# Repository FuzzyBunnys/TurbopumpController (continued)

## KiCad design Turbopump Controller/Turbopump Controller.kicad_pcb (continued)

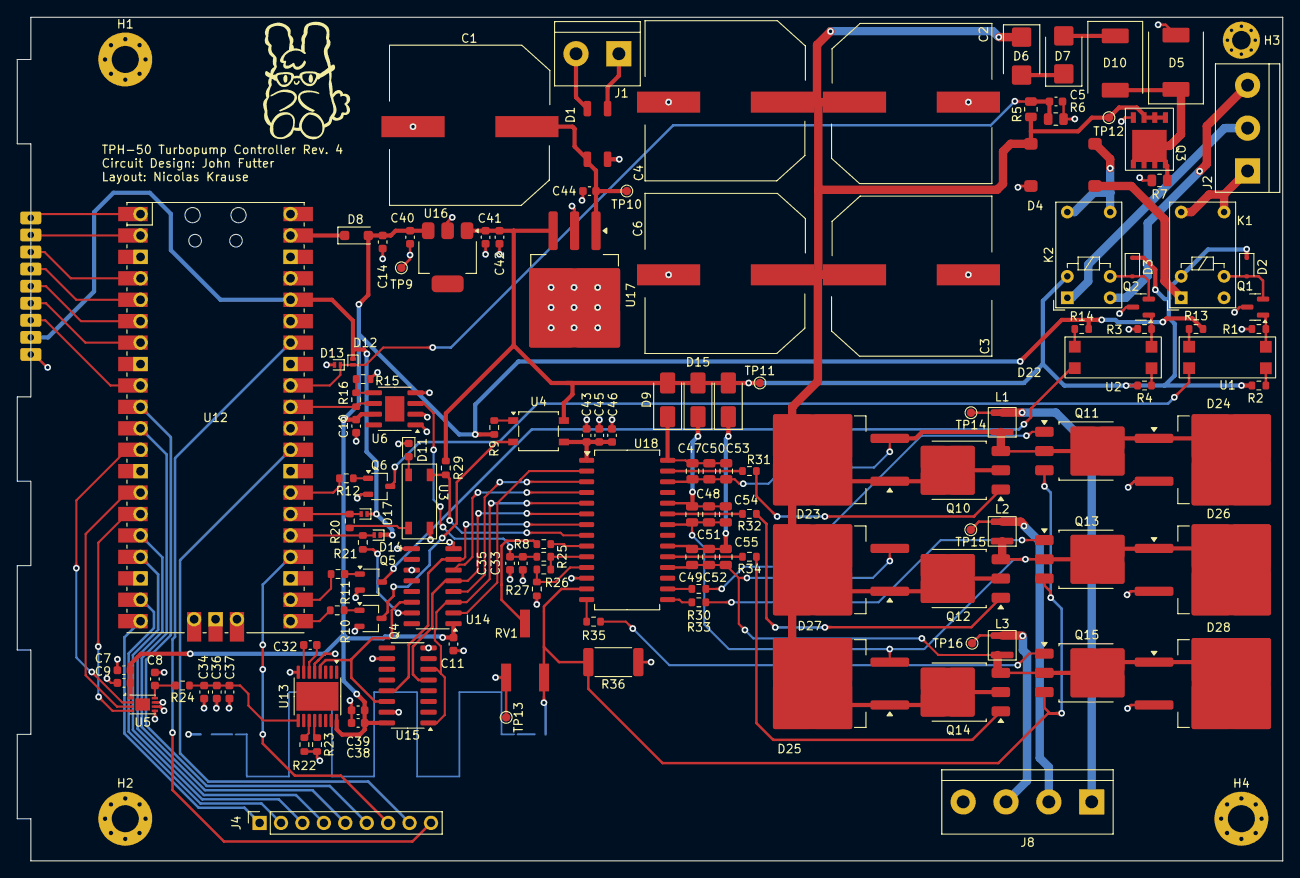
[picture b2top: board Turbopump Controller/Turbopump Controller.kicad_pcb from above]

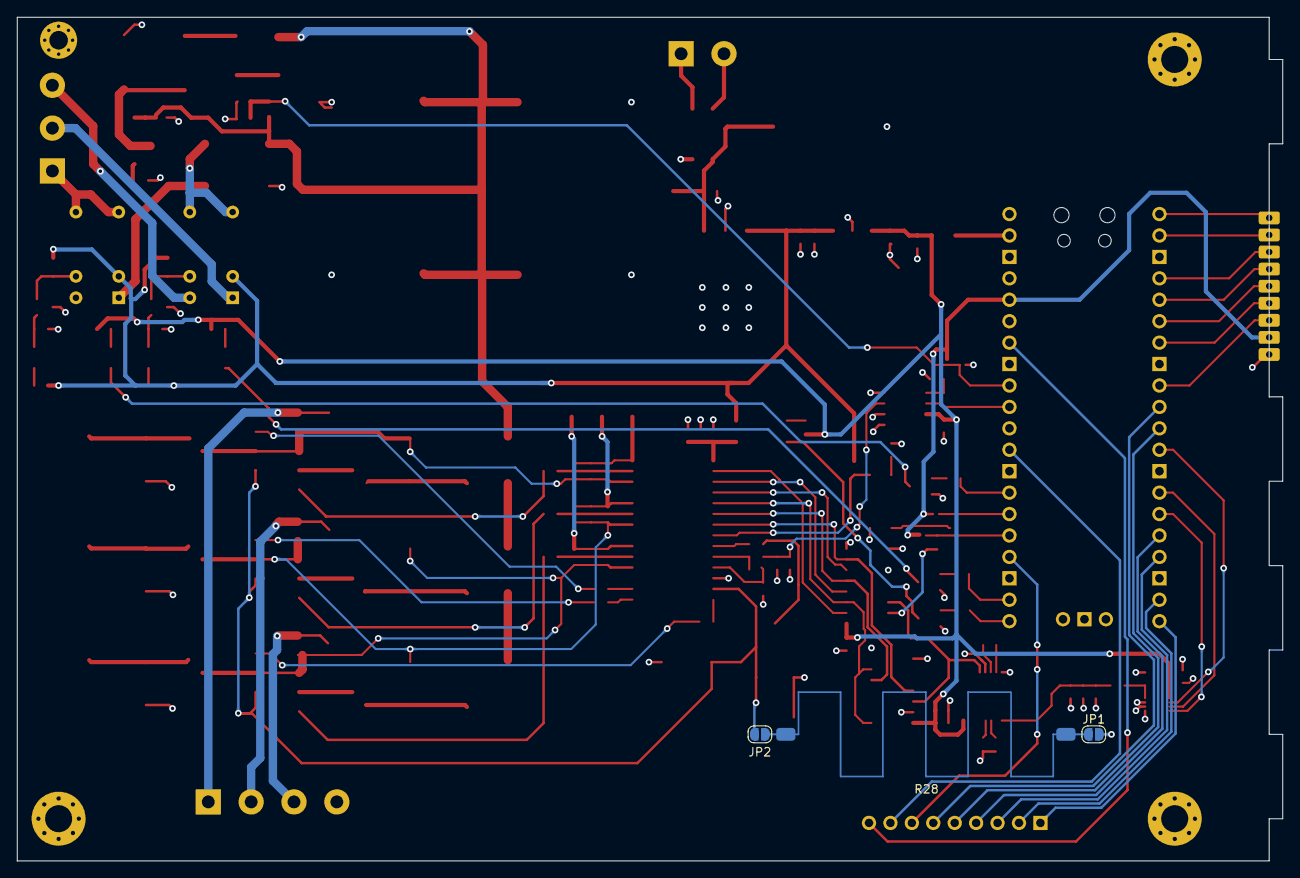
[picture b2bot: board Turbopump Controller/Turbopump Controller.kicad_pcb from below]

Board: 4 copper layers, 150.0 x 100.0 mm, 142 parts (3 on the bottom side), 106 nets.

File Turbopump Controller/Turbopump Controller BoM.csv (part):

"Source:","C:\Users\fuzzy\Documents\Fusor\Fusor Sensors\Turbopump Controller Complete\Turbopump Controller\Turbopump Controller.kicad_sch"
"Date:","2024-02-09 11:35:52 AM"
"Tool:","Eeschema (6.0.0)"
"Generator:","C:\Program Files\KiCad\6.0\bin\scripting\plugins/bom_csv_grouped_by_value.py"
"Component Count:","120"

"Individual Components:"

"Item","Qty","Reference(s)","Value","LibPart","Footprint","Datasheet"
"","","C1","330uF 100v","Device:C_Polarized_US","","~"
"","","C2","330uF 100v","Device:C_Polarized_US","","~"
"","","C3","330uF 100v","Device:C_Polarized_US","","~"
"","","C4","330uF 100v","Device:C_Polarized_US","","~"
"","","C5","0.1u","Device:C","Capacitor_SMD:C_0603_1608Metric_Pad1.08x0.95mm_HandSolder","~"
"","","C6","330uF 100v","Device:C_Polarized_US","","~"
"","","C7","0.1u","Device:C","","~"
"","","C8","1u","Device:C","","~"
"","","C9","10u","Device:C","","~"
"","","C14","4.7u","Device:C","Capacitor_SMD:C_0603_1608Metric_Pad1.08x0.95mm_HandSolder","~"
"","","C32","3.9n","Device:C","Capacitor_SMD:C_0603_1608Metric_Pad1.08x0.95mm_HandSolder","~"
"","","C33","4.7u","Device:C","Capacitor_SMD:C_0603_1608Metric_Pad1.08x0.95mm_HandSolder","~"
"","","C34","4.7u","Device:C","Capacitor_SMD:C_0603_1608Metric_Pad1.08x0.95mm_HandSolder","~"
"","","C35","4.7u","Device:C","Capacitor_SMD:C_0603_1608Metric_Pad1.08x0.95mm_HandSolder","~"
"","","C36","4.7u","Device:C","Capacitor_SMD:C_0603_1608Metric_Pad1.08x0.95mm_HandSolder","~"
"","","C37","4.7u","Device:C","Capacitor_SMD:C_0603_1608Metric_Pad1.08x0.95mm_HandSolder","~"
"","","C38","4.7u","Device:C","Capacitor_SMD:C_0603_1608Metric_Pad1.08x0.95mm_HandSolder","~"
"","","C39","4.7u","Device:C","Capacitor_SMD:C_0603_1608Metric_Pad1.08x0.95mm_HandSolder","~"
"","","C40","4.7u","Device:C","Capacitor_SMD:C_0603_1608Metric_Pad1.08x0.95mm_HandSolder","~"
"","","C41","4.7u","Device:C","Capacitor_SMD:C_0603_1608Metric_Pad1.08x0.95mm_HandSolder","~"
"","","C42","4.7u","Device:C","Capacitor_SMD:C_0603_1608Metric_Pad1.08x0.95mm_HandSolder","~"
"","","C43","4.7u","Device:C","Capacitor_SMD:C_0603_1608Metric_Pad1.08x0.95mm_HandSolder","~"
"","","C44","4.7u","Device:C","Capacitor_SMD:C_0603_1608Metric_Pad1.08x0.95mm_HandSolder","~"
"","","C45","4.7u","Device:C","Capacitor_SMD:C_0603_1608Metric_Pad1.08x0.95mm_HandSolder","~"
"","","C46","4.7u","Device:C","Capacitor_SMD:C_0603_1608Metric_Pad1.08x0.95mm_HandSolder","~"
"","","C47","4.7u","Device:C","Capacitor_SMD:C_0603_1608Metric_Pad1.08x0.95mm_HandSolder","~"
"","","C48","4.7u","Device:C","Capacitor_SMD:C_0603_1608Metric_Pad1.08x0.95mm_HandSolder","~"
"","","C49","4.7u","Device:C","Capacitor_SMD:C_0603_1608Metric_Pad1.08x0.95mm_HandSolder","~"
"","","C50","4.7u","Device:C","Capacitor_SMD:C_0603_1608Metric_Pad1.08x0.95mm_HandSolder","~"
"","","C51","4.7u","Device:C","Capacitor_SMD:C_0603_1608Metric_Pad1.08x0.95mm_HandSolder","~"
"","","C52","4.7u","Device:C","Capacitor_SMD:C_0603_1608Metric_Pad1.08x0.95mm_HandSolder","~"
"","","C53","4.7u","Device:C","Capacitor_SMD:C_0603_1608Metric_Pad1.08x0.95mm_HandSolder","~"
"","","C54","4.7u","Device:C","Capacitor_SMD:C_0603_1608Metric_Pad1.08x0.95mm_HandSolder","~"
"","","C55","4.7u","Device:C","Capacitor_SMD:C_0603_1608Metric_Pad1.08x0.95mm_HandSolder","~"
"","","D1","D_Bridge_+-AA","Device:D_Bridge_+-AA","Diode_SMD:Diode_Bridge_Vishay_DFSFlat","~"
"","","D2","D","Device:D","Diode_SMD:D_SOT-23_ANK","~"
"","","D3","D","Device:D","Diode_SMD:D_SOT-23_ANK","~"
"","","D4","D_Bridge_+-AA",":D_Bridge_+-AA_1","Diode_THT:Diode_Bridge_19.0x3.5x10.0mm_P5.0mm","~"
"","","D5","1.5KExxA","Diode:1.5KExxA","Diode_THT:D_DO-201AE_P15.24mm_Horizontal","https://www.vishay.com/docs/88301/15ke.pdf"
"","","D6","1.5KExxA","Diode:1.5KExxA","Diode_THT:D_DO-201AE_P15.24mm_Horizontal","https://www.vishay.com/docs/88301/15ke.pdf"
"","","D7","1.5KExxA","Diode:1.5KExxA","Diode_THT:D_DO-201AE_P15.24mm_Horizontal","https://www.vishay.com/docs/88301/15ke.pdf"
"","","D8","D_Schottky","Device:D_Schottky","Diode_SMD:D_0805_2012Metric_Pad1.15x1.40mm_HandSolder","~"
"","","D9","D","Device:D","Diode_SMD:D_SOT-23_ANK","~"
"","","D10","1.5KExxA","Diode:1.5KExxA","Diode_THT:D_DO-201AE_P15.24mm_Horizontal","https://www.vishay.com/docs/88301/15ke.pdf"
"","","D11","LED","Device:LED","LED_SMD:LED_0603_1608Metric","~"
"","","D15","D","Device:D","Diode_SMD:D_SOT-23_ANK","~"
"","","D22","D","Device:D","Diode_SMD:D_SOT-23_ANK","~"
"","","D23","HFA04TB60","TurbopumpLibrary:HFA04TB60","Package_TO_SOT_SMD:TO-263-2",""
"","","D24","HFA04TB60","TurbopumpLibrary:HFA04TB60","Package_TO_SOT_SMD:TO-263-2",""
"","","D25","HFA04TB60","TurbopumpLibrary:HFA04TB60","Package_TO_SOT_SMD:TO-263-2",""
"","","D26","HFA04TB60","TurbopumpLibrary:HFA04TB60","Package_TO_SOT_SMD:TO-263-2",""
"","","D27","HFA04TB60","TurbopumpLibrary:HFA04TB60","Package_TO_SOT_SMD:TO-263-2",""
"","","D28","HFA04TB60","TurbopumpLibrary:HFA04TB60","Package_TO_SOT_SMD:TO-263-2",""
"","","J1","Conn_01x02","Connector_Generic:Conn_01x02","Connector_PinSocket_2.54mm:PinSocket_1x02_P2.54mm_Vertical","~"
"","","J2","Conn_01x03","Connector_Generic:Conn_01x03","Connector_PinSocket_2.54mm:PinSocket_1x03_P2.54mm_Vertical","~"
"","","J3","Conn_01x08","Connector_Generic:Conn_01x08","","~"
"","","J6","Conn_01x06","Connector_Generic:Conn_01x06","Connector_PinSocket_2.54mm:PinSocket_1x06_P2.54mm_Vertical","~"
"","","J7","Conn_01x02","Connector_Generic:Conn_01x02","Connector_PinSocket_2.54mm:PinSocket_1x02_P2.54mm_Vertical","~"
"","","J8","Conn_01x04","Connector_Generic:Conn_01x04","Connector_PinSocket_2.54mm:PinSocket_1x04_P2.54mm_Vertical","~"
"","","K1","RT314A03","Relay:RT314A03","TpumpLib:Relay_SPDT_J102_CitRelay_RM3.5mm","https://www.te.com/commerce/DocumentDelivery/DDEController?A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"
"","","K2","RT314A03","Relay:RT314A03","TpumpLib:Relay_SPDT_J102_CitRelay_RM3.5mm","https://www.te.com/commerce/DocumentDelivery/DDEController?A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"
"","","L1","3.9 uH","Device:L_Iron","","~"
"","","L2","3.9 uH","Device:L_Iron","","~"
"","","L3","3.9 uH","Device:L_Iron","","~"
"","","Q1","Q_NPN_BCE","Device:Q_NPN_BCE","Package_TO_SOT_SMD:SOT-23","~"
"","","Q2","Q_NPN_BCE","Device:Q_NPN_BCE","Package_TO_SOT_SMD:SOT-23","~"
"","","Q3","Q_NMOS_DSG","Device:Q_NMOS_DSG","Package_TO_SOT_THT:TO-3P-3_Vertical","~"
"","","Q10","IRG4PF50W","Transistor_IGBT:IRG4PF50W","Package_TO_SOT_SMD:TO-252-3_TabPin2","http://www.irf.com/product-info/datasheets/data/irg4pf50w.pdf"
"","","Q11","IRG4PF50W","Transistor_IGBT:IRG4PF50W","Package_TO_SOT_SMD:TO-252-3_TabPin2","http://www.irf.com/product-info/datasheets/data/irg4pf50w.pdf"
"","","Q12","IRG4PF50W","Transistor_IGBT:IRG4PF50W","Package_TO_SOT_SMD:TO-252-3_TabPin2","http://www.irf.com/product-info/datasheets/data/irg4pf50w.pdf"
"","","Q13","IRG4PF50W","Transistor_IGBT:IRG4PF50W","Package_TO_SOT_SMD:TO-252-3_TabPin2","http://www.irf.com/product-info/datasheets/data/irg4pf50w.pdf"
"","","Q14","IRG4PF50W","Transistor_IGBT:IRG4PF50W","Package_TO_SOT_SMD:TO-252-3_TabPin2","http://www.irf.com/product-info/datasheets/data/irg4pf50w.pdf"
"","","Q15","IRG4PF50W","Transistor_IGBT:IRG4PF50W","Package_TO_SOT_SMD:TO-252-3_TabPin2","http://www.irf.com/product-info/datasheets/data/irg4pf50w.pdf"
"","","R1","100K","Device:R","Resistor_SMD:R_0603_1608Metric","~"
"","","R2","6.8K","Device:R","Resistor_SMD:R_0603_1608Metric","~"
"","","R3","100K","Device:R","Resistor_SMD:R_0603_1608Metric","~"
"","","R4","6.8K","Device:R","Resistor_SMD:R_0603_1608Metric","~"
"","","R5","150K","Device:R","Resistor_THT:R_Axial_DIN0204_L3.6mm_D1.6mm_P7.62mm_Horizontal","~"
"","","R6","10K","Device:R","Resistor_THT:R_Axial_DIN0204_L3.6mm_D1.6mm_P7.62mm_Horizontal","~"
"","","R7","10K","Device:R","Resistor_THT:R_Axial_DIN0204_L3.6mm_D1.6mm_P7.62mm_Horizontal","~"
"","","R8","1K","Device:R","Resistor_SMD:R_0603_1608Metric","~"
"","","R22","22K","Device:R","Resistor_SMD:R_0603_1608Metric","~"
"","","R23","1M","Device:R","Resistor_SMD:R_0603_1608Metric","~"
"","","R24","470K","Device:R","Resistor_SMD:R_0603_1608Metric","~"
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
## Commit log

2022-04-16 Set theme jekyll-theme-minimal
2023-12-10 Update index.md
    added kicad files and kicanvas link
2024-02-26 Delete Turbopump Controller directory
    Updating to new version
2024-02-26 Add files via upload
    new version of schematic
2024-02-26 Add files via upload
    New Tpump Schematic
